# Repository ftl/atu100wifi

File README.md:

# atu100wifi

This is a little extension device for David Fainitski's [ATU-100](https://github.com/Dfinitski/N7DDC-ATU-100-mini-and-extended-boards) antenna tuner. It adds connectivity though wifi to use the tuner in a remote setup. The software publishes all measurement data using MQTT and accepts remote commands through another MQTT topic.

The device replaces the tuner's display. It communicates with the ATU-100 through it's I2C bus to grasp all the measurement data. An Arduino Nano acts as I2C slave, listening with the display's address, and interpreting the rendering commands coming from the ATU-100. The Nano sends the display content to an ESP8266 [WeMos D1 mini](https://www.wemos.cc/en/latest/d1/d1_mini.html), where the data is parsed, packed into a JSON object and published to a MQTT topic.

This project uses PlatformIO to build the software for the MCUs.

## Disclaimer
I develop this device for myself and just for fun in my free time. If you find it useful, I'm happy to hear about that. If you have trouble using it, you have all the source code to fix the problem yourself (although pull requests are welcome).

I am not liable for whatever happens to you by building or using this device. Do this on your own risk!

## License
This tool is published under the [MIT License](https://www.tldrlegal.com/l/mit).

Copyright [Florian Thienel](http://thecodingflow.com/)

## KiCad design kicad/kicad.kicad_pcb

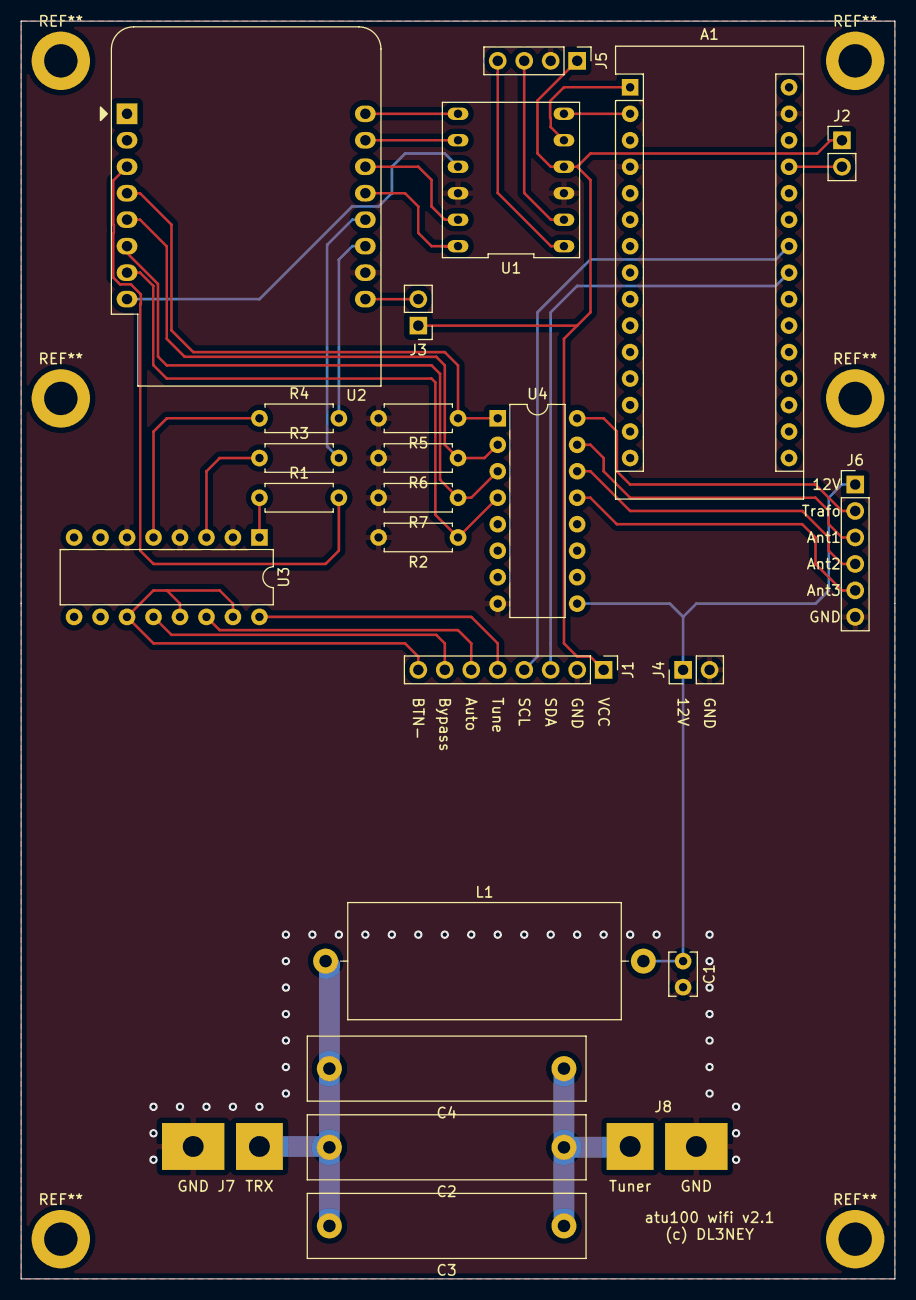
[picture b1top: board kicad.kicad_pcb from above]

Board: 2 copper layers, 83.8 x 120.7 mm, 25 parts (0 on the bottom side), 36 nets.

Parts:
A1: Arduino_Nano_v3.x; Arduino_Nano
C1: 100n; C_Rect_L4.0mm_W2.5mm_P2.50mm
C2, C3, C4: 10n; C_Rect_L26.5mm_W6.0mm_P22.50mm_MKS4
J1: ATU100; PinHeader_1x08_P2.54mm_Vertical
J2, J3: Conn_01x02_Male; PinHeader_1x02_P2.54mm_Vertical
J4: ATU100_12V; PinHeader_1x02_P2.54mm_Vertical
J5: Display/I2C; PinHeader_1x04_P2.54mm_Vertical
J6: Ant Switch; PinHeader_1x06_P2.54mm_Vertical
J7: TRX; SolderWirePad_1x02_P7.62mm_Drill2mm
J8: Tuner; SolderWirePad_1x02_P7.62mm_Drill2mm
L1: 1m; L_Axial_L26.0mm_D11.0mm_P30.48mm_Horizontal_Fastron_77A
R1, R3, R4: 470; R_Axial_DIN0207_L6.3mm_D2.5mm_P7.62mm_Horizontal
R2, R5, R6, R7: 10k; R_Axial_DIN0207_L6.3mm_D2.5mm_P7.62mm_Horizontal
U1: 4Bit_China_Level_Shifter
U2: WeMos_D1_mini; WEMOS_D1_mini_light
U3: LTV-847; DIP-16_W7.62mm
U4: ULN2004A; DIP-16_W7.62mm

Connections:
+3V3: U1.9, U2.8
+12V: C1.1, J4.1, J6.1, L1.2, U4.9
Ant1: J6.3, U4.15
Ant2: J6.4, U4.14
Ant3: J6.5, U4.13
BTN-: J1.8, U3.11, U3.13, U3.15
BTNAuto+: J1.6, U3.14
BTNByp+: J1.7, U3.12
BTNTune+: J1.5, U3.16
D0: R1.2, U2.3
D1: U1.11, U2.14
D2: U1.12, U2.13
D3: R3.2, U2.12
D4: R4.2, U2.11
D5: R5.1, U2.4, U4.1
D6: R6.1, U2.5, U4.2
D7: R7.1, U2.6, U4.3
D8: R2.1, U2.7, U4.4
GND: A1.4, A1.29, C1.2, J1.2, J4.2, J5.2, J6.6, J7.2, J8.2, R2.2, R5.2, R6.2, R7.2, U1.3, U1.10, U2.10, U3.2, U3.4, U3.6, U4.8
unnamed: A1.1, U1.5
unnamed: A1.2, U1.6
unnamed: A1.27, J2.2
unnamed: C2.1, C3.1, C4.1, J8.1
unnamed: C2.2, C3.2, C4.2, J7.1, L1.1
unnamed: J3.2, U2.9
unnamed: R1.1, U3.1
unnamed: R3.1, U3.3
unnamed: R4.1, U3.5
unnamed: U1.7, U2.16
unnamed: U1.8, U2.15
SCL: A1.24, J1.4
SCL2: J5.4, U1.1
SDA: A1.23, J1.3
SDA2: J5.3, U1.2
Trafo: J6.2, U4.16
VCC: J1.1, J2.1, J3.1, J5.1, U1.4

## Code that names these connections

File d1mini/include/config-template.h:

/*
    This header contains all the configuration data.
*/

#define WIFI_SSID "myssid"
#define WIFI_PASSPHRASE "mysecretpassphrase"
#define WIFI_HOSTNAME "myatu100"
// uncomment to use the built-in LED to indicate the WIFI status
// ATTENTION: this collides with the support for the BYPASS button. 
// If you use WIFI_LED, do NOT connect the BYPASS button!
// #define WIFI_LED

#define MQTT_HOST "192.168.1.1"
#define MQTT_PORT 1883
#define MQTT_CLIENT_ID "atu100"
#define MQTT_USER ""
#define MQTT_PASSWORD ""
#define MQTT_DATA_TOPIC "hamradio/atu100/data"
#define MQTT_RSSI_TOPIC "hamradio/atu100/rssi"
#define MQTT_WILL_TOPIC "hamradio/atu100/alive"
#define MQTT_CMD_TOPIC "hamradio/atu100/cmd"
#define MQTT_TRAFO_RELAY_TOPIC "afu/atu100/relays/trafo"
#define MQTT_ANT1_RELAY_TOPIC "afu/atu100/relays/ant1"
#define MQTT_ANT2_RELAY_TOPIC "afu/atu100/relays/ant2"
#define MQTT_ANT3_RELAY_TOPIC "afu/atu100/relays/ant3"

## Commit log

2020-08-07 set the hostname
2020-08-07 make thicker wires to make soldering of routed pcbs easier
2020-11-17 add output to switch an external relay with an external voltage
2020-11-23 first attempt to leverage all IOs in order to support all three possible buttons and an external antenna switch
2020-11-29 move the 12V connector for the atu100 next to the control signal connector
2020-12-21 use the ULN2003, stupid
2020-12-21 add support for one trafo and three antenna relays
